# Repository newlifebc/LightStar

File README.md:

# LightStar
LightStar PCB and Firmware for 2019 Christmas Show

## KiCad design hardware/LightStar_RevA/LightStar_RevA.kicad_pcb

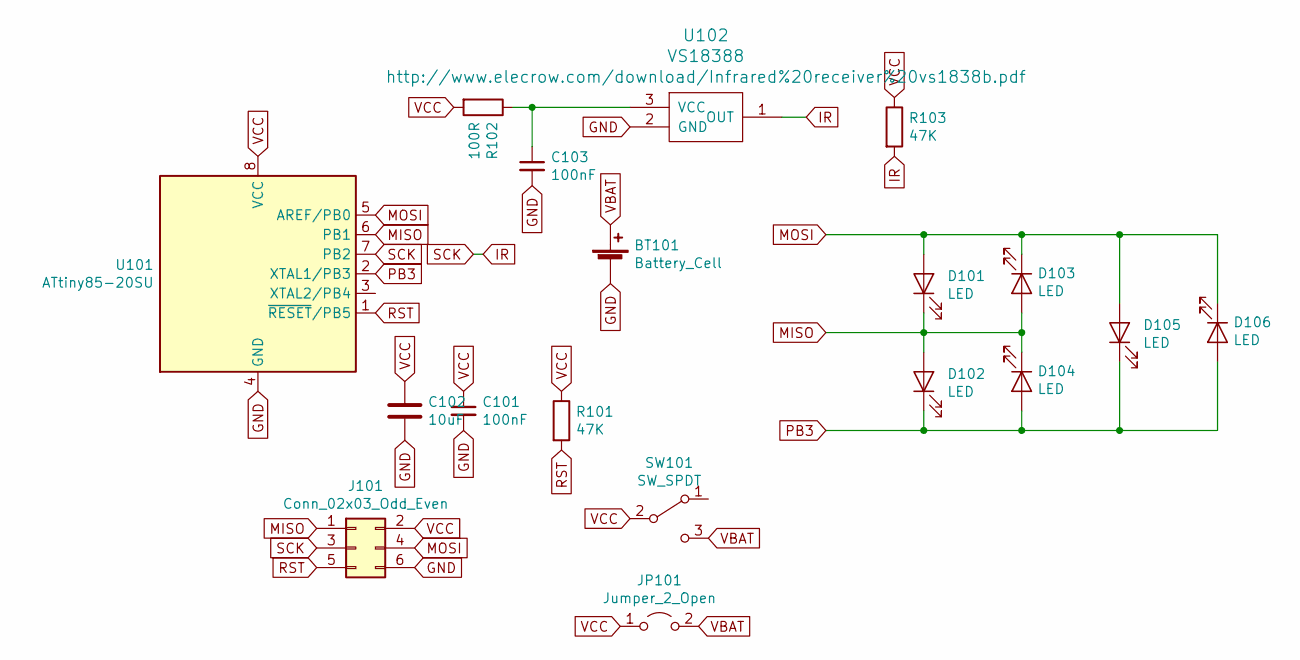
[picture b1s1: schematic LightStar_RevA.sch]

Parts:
BT101: Battery_Cell; BatteryHolder_Keystone_1060_1x2032
C101, C103: 100nF; C_0603_1608Metric
C102: 10uF; C_0805_2012Metric
D101, D102, D103, D104, D105, D106: LED; LED_D5.0mm
J101: Conn_02x03_Odd_Even; PinHeader_2x03_P2.54mm_Vertical
JP101: Jumper_2_Open; SolderJumper-2_P1.3mm_Open_RoundedPad1.0x1.5mm
R101, R103: 47K; R_0805_2012Metric
R102: 100R; R_0805_2012Metric
SW101: SW_SPDT; SW_SPDT_PCM12
U101: ATtiny85-20SU; SOIJ-8_5.3x5.3mm_P1.27mm
U102: VS18388; VS1838B

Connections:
GND: BT101.2 (-), C101.2, C102.2, C103.2, J101.6, U101.4 (GND), U102.2 (GND)
IR: J101.3, R103.2, U101.7 (PB2), U102.1 (OUT)
MISO: D101.1 (K), D102.2 (A), D103.2 (A), D104.1 (K), J101.1, U101.6 (PB1)
MOSI: D101.2 (A), D103.1 (K), D105.2 (A), D106.1 (K), J101.4, U101.5 (AREF/PB0)
unnamed: C103.1, R102.1, U102.3 (VCC)
PB3: D102.1 (K), D104.2 (A), D105.1 (K), D106.2 (A), U101.2 (XTAL1/PB3)
RST: J101.5, R101.2, U101.1 (~RESET~/PB5)
VBAT: BT101.1 (+), JP101.2 (B), SW101.3 (C)
VCC: C101.1, C102.1, J101.2, JP101.1 (A), R101.1, R102.2, R103.1, SW101.2 (B), U101.8 (VCC)

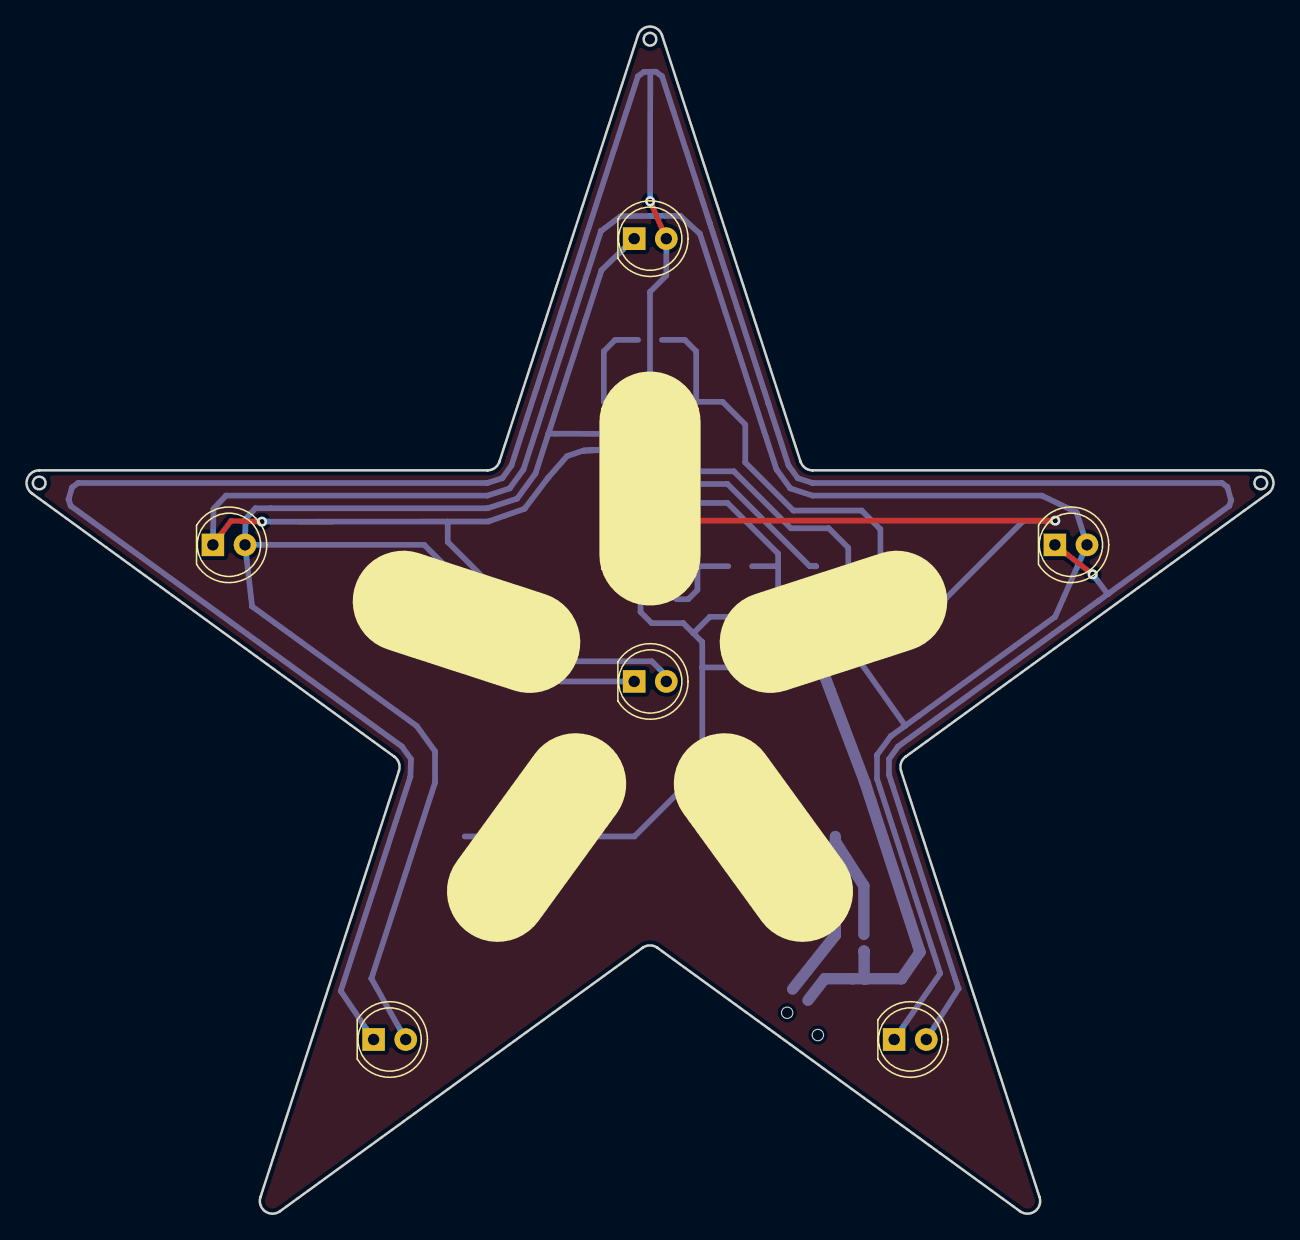
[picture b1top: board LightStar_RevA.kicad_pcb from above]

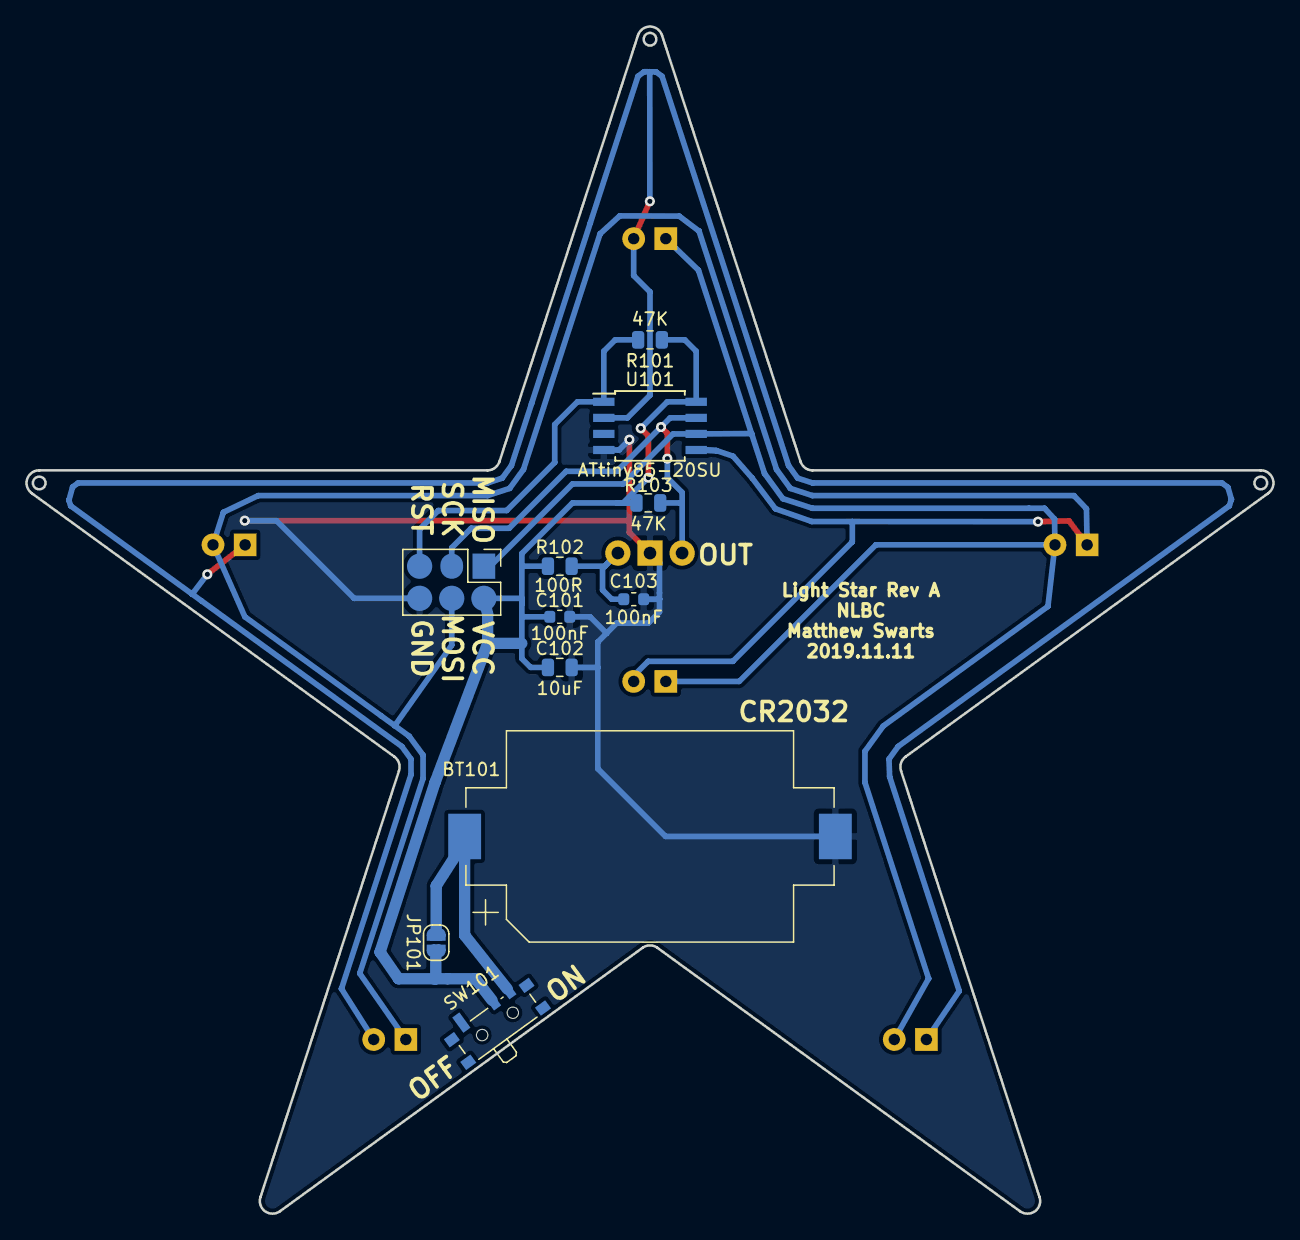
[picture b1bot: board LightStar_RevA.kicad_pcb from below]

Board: 2 copper layers, 98.6 x 93.8 mm, 18 parts (11 on the bottom side), 9 nets.

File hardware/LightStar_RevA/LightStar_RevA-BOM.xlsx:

UPN | PART | DESC | QTY | Hyperlink | Unit Cost with Shipping | SubTotal | 3.3229000000000006
UPN-01 |  | PCB, White, 0.6mm, HASL PB Free | 1 |  | 1 | 1
UPN-02 |  | CR2032 Battery | 1 | https://www.digikey.com/product-detail/en/panasonic-bsg/CR20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 | 0.34 | 0.34
UPN-03 | BT101 | CR2032 Retainer 3002 | 1 | https://lcsc.com/product-detail/Battery-Holders-Clips-Contac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 | 0.1348 | 0.1348
UPN-04 | C101,C103 | 100nF capacitor 0603 | 2 | https://lcsc.com/product-detail/Multilayer-Ceramic-Capacitor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 | 5.8999999999999999E-3 | 1.18E-2
UPN-05 | C102 | 10uF capacitor 0805 | 1 | https://lcsc.com/product-detail/Multilayer-Ceramic-Capacitor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 | 1.3100000000000001E-2 | 1.3100000000000001E-2
UPN-06 | D101-D106 | White LED 5mm | 6 | https://lcsc.com/product-detail/Light-Emitting-Diodes-LED_wh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 | 5.62E-2 | 0.3372
UPN-07 | R102 | 100R resistor 0805 | 2 | https://lcsc.com/product-detail/Chip-Resistor-Surface-Mount_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 | 2.7000000000000001E-3 | 5.4000000000000003E-3
UPN-08 | R101,R103 | 47K resistor 0805 | 1 | https://lcsc.com/product-detail/Chip-Resistor-Surface-Mount_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 | 2.7000000000000001E-3 | 2.7000000000000001E-3
UPN-09 | SW101 | PCM12, 7PIN | 1 | https://lcsc.com/product-detail/Toggle-Switches_ALPS_SSSS811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 | 0.10290000000000001 | 0.10290000000000001
UPN-10 | U101 | ATtiny45 SMD | 1 | https://lcsc.com/product-detail/MICROCHIP_MICROCHIP_ATTINY45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 | 1.3 | 1.3
UPN-11 | U102 | VS1838B | 1 | https://www.aliexpress.com/item/32393261763.html | 7.4999999999999997E-2 | 7.4999999999999997E-2

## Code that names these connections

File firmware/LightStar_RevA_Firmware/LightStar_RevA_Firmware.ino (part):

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//#include <IRLibRecvPCI.h> 

/*
PB0 MOSI 0
PB1 MISO 1
PB2 SCK  2 INT0 - IR INPUT
PB3      3 
PB4      4 -none

        PB0   PB1   PB3
LED101  HIGH  LOW   FLOAT
LED102  FLOAT HIGH  LOW
LED103  LOW   HIGH  FLOAT
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
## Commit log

2019-12-19 initial commit of existing files
2019-12-19 cleaned up and timed firmware to wrowk with song at 1MHz internal speed to allow longer battery life
2019-12-22 minor update
